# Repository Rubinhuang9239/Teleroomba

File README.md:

# Teleroomba

<h2>Info</h2>

A telepresence researching project that build for NYU NYC/Abu Dhabi/Shanghai campus.<br />
Thanks to Open Source Hardware Community, we hacked iRobot-Create roomba with Arduino(DFRobot Bluno), and created a telepresence robot.

<br/><br/>
This repo coontains the source code of the original project.
<br/>
For more documentation of this project, please visit: www.rubinhuang.com/#teleroomba

<h2>History + Future Development</h2>

<b>Teleroomba 1.x</b>

A 2D video and real time communication telepresence robot

<br />
The following image provides the concept of this project(teleroomba 1.x).<br/>

<br/>

It’s a roomba based robot which controlled from a web + Android + Arduino system.
User can control the robot from a web browser with keyboard input/mouse/touch screen.

<b>Teleroomba 2.x</b>

A 2D/3D video and real time communication telepresence robot

It’s a roomba based robot which controlled from a web + Android + Arduino system.
With the power of Lattepanda and Linux, this model is able to live stream a UV map from 360 camera like thetaS.

User can control the robot from a web browser with keyboard input/mouse/touch screen.
An individual window will stream the 360 video.

<b>Teleroomba 3.x</b>

A 2D/3D video and real time communication telepresence robot

A fully integrated system on Linux runs on lattepanda/raspberry Pi
support multi HDMI-Input/output, connect to live stream engine, webGL and even Unity game features.

<h2>Software and hardware structure</h2>
The following imgae shows current version of teleroomba(2.x)

<h2>Video and documentations</h2>

documented over iterations
<br/>
<b>Teleroomba 1.x</b>
<br/>
Video
<br/>

<br/>
Details
<br/>

<br/><br/>
<b>Teleroomba 2.x</b>
<br/>
Lattepanda + Node.js
<br/>

<h5>Circuit</h5>
<h5>Interface</h5>
More documentation in this link

<br /><br />
<h2>Hacking of the iRobot</h2>

<h3>Hacking documentation in google slides:</h3>

https://docs.google.com/presentation/d/1esRmssKKQKUmZPN4M6qO2HnMcj071nKUZhuvG29GHJI/edit?usp=sharing

<h3>Offical iRobot® Create® 2 Open Interface (OI):</h3>

http://www.irobotweb.com/~/media/MainSite/PDFs/About/STEM/Create/iRobot_Roomba_600_Open_Interface_Spec.pdf?la=en

<h2>Build</h2>
<a href = "https://github.com/Rubinhuang9239/Teleroomba/wiki/1.x-build-wiki">see 1.x build wiki</a>
<br/>
<a href = "https://github.com/Rubinhuang9239/Teleroomba/wiki/2.x-build-wiki">see 2.x build wiki</a>
<br/>

<h3>Control Manual</h3>
You can connect to turn server and call the mobile device on roomba(default auto connect and call) and establish bluetooth connection between the device & Roomba's serial port from control terminal. Full manual list here:
<br />
<ol>
<li>Connect with id</li>
<li>Call device with id</li>
<li>Bluno BLE scan</li>
<li>Restart safty mode</li>
<li>Serial board reset</li>
<li>Auto Docking</li>
</ol>

<h3>HUD display</h3>
<b>Distance</b>
A group of lines accroded to the perspective of the lense for helping driver to estimate the distance.

<b>Direction</b>
A rough predict of your crusing path, it will only show turning sign when roomba is doing same spot turning.

<h2>Credits + Resource</h2>

<h3>Credits + Thanks:</h3>
Early contributor:<br />
Rubin Huang<br />
Marc Abbey

Advising:<br />
Dan O'sullivan<br />
Shawn Van Every<br />

<h3>Current API:</h3>
coming soon....

<h3>More related projects:</h3>

<h5>From iRobot.com</h5>
http://www.irobot.com/About-iRobot/STEM/Create-2/Projects.aspx

<h5>From random hackers:</h5>

Johnny Chung Lee's DIY Telepresence Robot(2011)
with source code and intruductions
http://procrastineering.blogspot.com/2011/02/low-cost-video-chat-robot.html

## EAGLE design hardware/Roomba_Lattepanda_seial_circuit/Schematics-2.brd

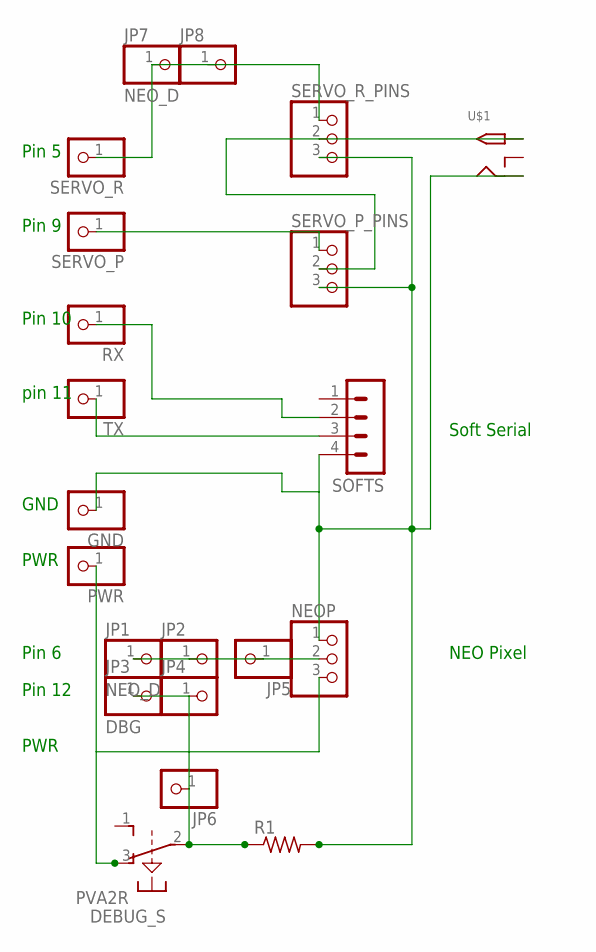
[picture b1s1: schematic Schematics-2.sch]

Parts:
DEBUG_S: PVA2R
GND: PINHD-1X1CB; 1X01-CLEANBIG
JP1, JP7: NEO_D; 1X01-CLEANBIG
JP2, JP4, JP5, JP6, JP8: PINHD-1X1CB; 1X01-CLEANBIG
JP3: DBG; 1X01-CLEANBIG
NEOP: PINHD-1X3CB; 1X03-CLEANBIG
PWR: PINHD-1X1CB; 1X01-CLEANBIG
R1: R-US_0204/7; 0204/7
RX: PINHD-1X1CB; 1X01-CLEANBIG
SERVO_P: PINHD-1X1CB; 1X01-CLEANBIG
SERVO_P_PINS: PINHD-1X3CB; 1X03-CLEANBIG
SERVO_R: PINHD-1X1CB; 1X01-CLEANBIG
SERVO_R_PINS: PINHD-1X3CB; 1X03-CLEANBIG
SOFTS: MA04-1
TX: PINHD-1X1CB; 1X01-CLEANBIG
U$1: 2.1MMJACKTHM; PJ-102A

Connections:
unnamed: RX.1, SOFTS.2
unnamed: JP1.1, JP2.1, JP5.1, NEOP.2
unnamed: SOFTS.3, TX.1
unnamed: GND.1, NEOP.1, R1.2, SERVO_P_PINS.3, SERVO_R_PINS.3, SOFTS.4, U$1.RING
unnamed: DEBUG_S.3 (O), NEOP.3, PWR.1
unnamed: DEBUG_S.2, JP3.1, JP4.1, JP6.1, R1.1
unnamed: SERVO_P_PINS.2, SERVO_R_PINS.2, U$1.TIP
unnamed: JP7.1, JP8.1, SERVO_R.1, SERVO_R_PINS.1
unnamed: SERVO_P.1, SERVO_P_PINS.1

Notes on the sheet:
Pin 10
pin 11
Pin 6
PWR
GND
Pin 12
Soft Serial
NEO Pixel
Pin 5
Pin 9

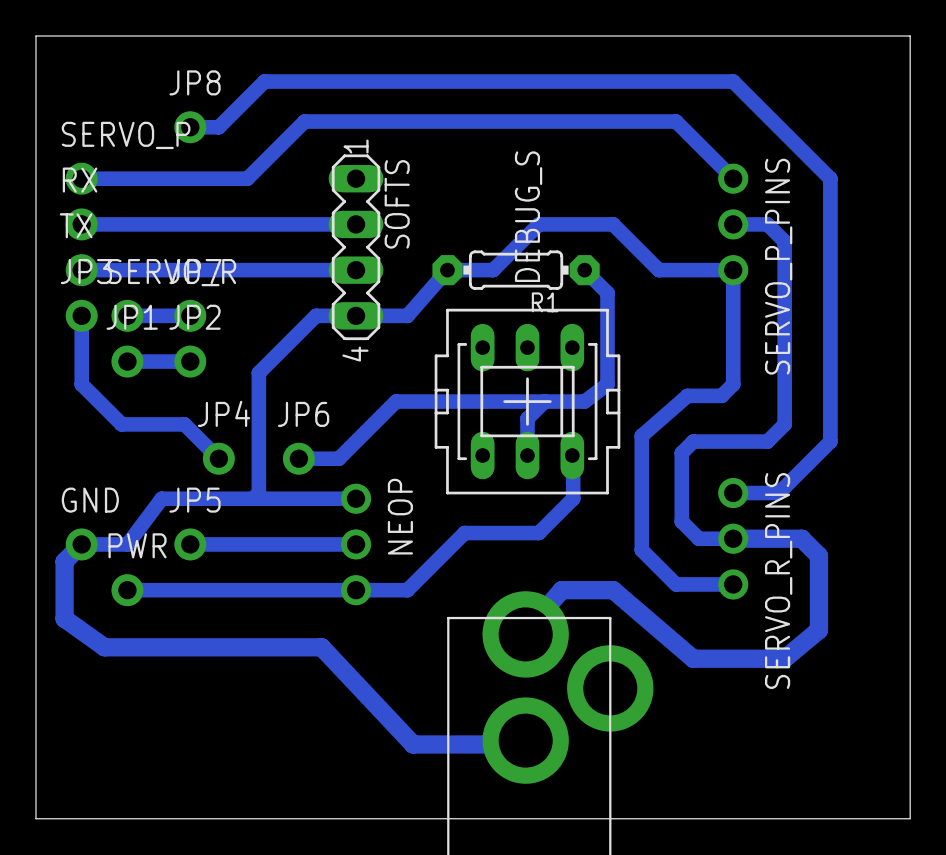
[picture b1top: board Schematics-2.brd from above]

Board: 2 copper layers, 48.6 x 43.5 mm, 21 parts (0 on the bottom side), 9 nets.

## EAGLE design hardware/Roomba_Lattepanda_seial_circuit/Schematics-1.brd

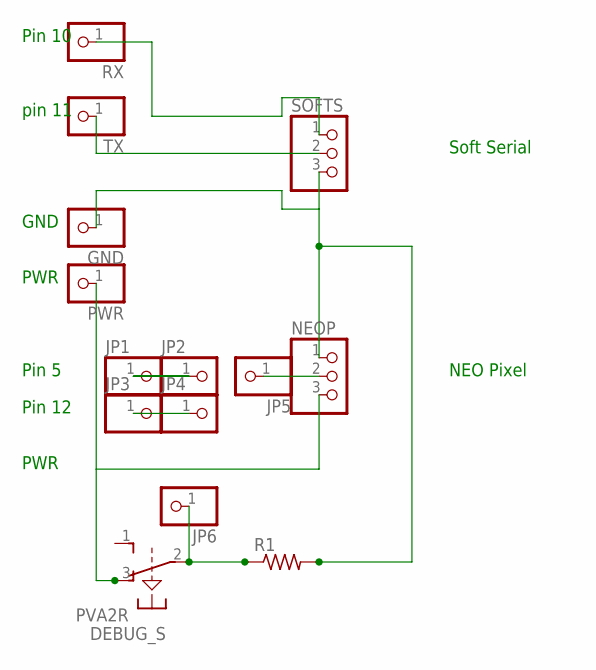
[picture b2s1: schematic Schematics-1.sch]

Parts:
DEBUG_S: PVA2R
GND: PINHD-1X1CB; 1X01-CLEANBIG
JP1, JP2, JP3, JP4, JP5, JP6: PINHD-1X1CB; 1X01-CLEANBIG
NEOP: PINHD-1X3CB; 1X03-CLEANBIG
PWR: PINHD-1X1CB; 1X01-CLEANBIG
R1: R-US_0204/7; 0204/7
RX: PINHD-1X1CB; 1X01-CLEANBIG
SOFTS: PINHD-1X3CB; 1X03-CLEANBIG
TX: PINHD-1X1CB; 1X01-CLEANBIG

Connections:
unnamed: RX.1, SOFTS.1
unnamed: JP1.1, JP2.1
unnamed: SOFTS.2, TX.1
unnamed: GND.1, NEOP.1, R1.2, SOFTS.3
unnamed: DEBUG_S.3 (O), NEOP.3, PWR.1
unnamed: DEBUG_S.2, JP6.1, R1.1
unnamed: JP5.1, NEOP.2
unnamed: JP3.1, JP4.1

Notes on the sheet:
Pin 10
pin 11
Pin 5
PWR
GND
Pin 12
Soft Serial
NEO Pixel

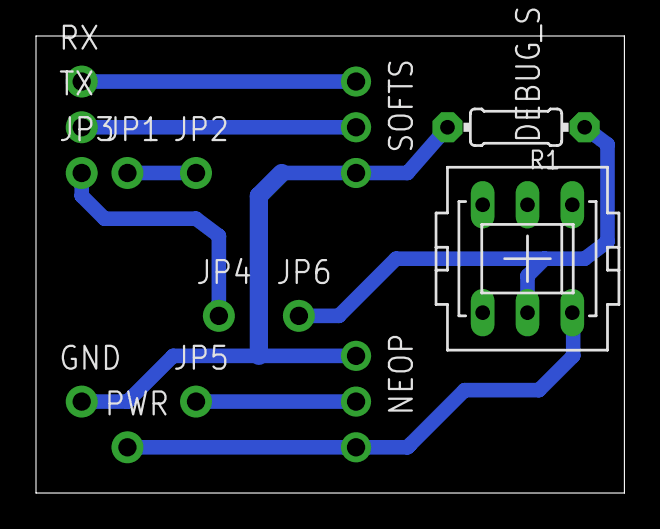
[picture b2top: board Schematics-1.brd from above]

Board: 2 copper layers, 32.7 x 25.4 mm, 14 parts (0 on the bottom side), 8 nets.

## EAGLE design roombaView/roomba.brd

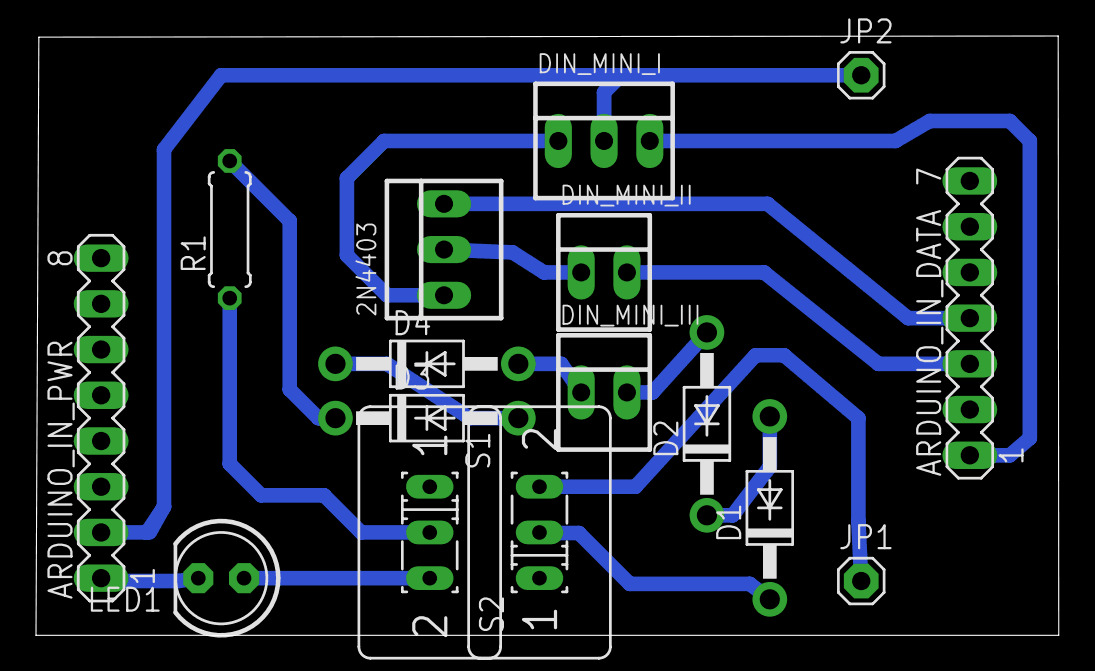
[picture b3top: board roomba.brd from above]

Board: 2 copper layers, 56.8 x 33.3 mm, 16 parts (0 on the bottom side), 16 nets.

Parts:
2N4403: 22-23-2031
ARDUINO_IN_DATA: MA07-1
ARDUINO_IN_PWR: MA08-1
D1, D2, D3, D4: 1N4001; DO41-10
DIN_MINI_I: 22-23-2031
DIN_MINI_II: 22-23-2021
DIN_MINI_III: 22-23-2021
JP1, JP2: 1X01
LED1: LED5MM
R1: 0207/7
S1, S2: M251

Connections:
unnamed: 2N4403.2, DIN_MINI_II.1
unnamed: 2N4403.1, DIN_MINI_I.1
unnamed: R1.1, S1.2
unnamed: D3.A, D4.C
unnamed: ARDUINO_IN_PWR.2, DIN_MINI_I.2, JP2.1
unnamed: 2N4403.3, ARDUINO_IN_DATA.4
unnamed: ARDUINO_IN_DATA.1, DIN_MINI_I.3
unnamed: ARDUINO_IN_DATA.3, DIN_MINI_II.2
unnamed: D4.A, DIN_MINI_III.1
unnamed: D2.A, DIN_MINI_III.2
unnamed: D1.A, D2.C
unnamed: LED1.A, S1.3
unnamed: ARDUINO_IN_PWR.1, LED1.K
unnamed: D1.C, S2.2
unnamed: D3.C, R1.2
unnamed: JP1.1, S2.3

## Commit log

2016-03-10 update app
2016-03-13 update source
2016-03-15 update with cordova
2016-03-27 update board
2016-04-07 adding slides
2016-04-07 update path structure
2016-04-07 adding oi
2016-04-07 add projects
2016-04-07 update readme....
2016-04-08 update WEBRTC source code
    yay
2016-04-08 update connection
    Auto BLE
2016-04-10 update documentation and folder structure
2016-04-16 add arts
2016-04-16 edit documentations
2016-04-16 update art
2016-04-18 upload arts
2016-04-25 push code
2016-05-09 https update
2016-06-01 update ble signs
2016-08-09 update local
    update local http/https;
    add 360 sphere view and webrtc connection
    add panda and webrtc connection
    add /role to express
    update panda, roomba, control, 360 with identity setup
    update roomba.js routing
2016-08-10 update video
2016-08-10 update file type
2016-08-10 add pandaServer prototype
2016-08-10 update 360 solution diagram
2016-08-10 panda_socket_to_serial
2016-10-01 update lattepanda arduino code
2016-10-02 update lattepanda arduino sys
2016-10-10 local server
2016-10-13 bug free serial
2016-10-14 update media player
2016-10-14 play remotely
2016-10-21 add new board/ add perfect stitch helper
2016-10-21 upload laser drawings
2016-10-23 add HUD
2016-10-23 add guide line and text
2016-10-24 update angle display / list display
2016-10-24 add reset Cam
2016-10-28 add resize function
2016-10-31 complete 360 stitchHelper
2016-11-01 full 360
2016-11-03 add ex 3d pro
2016-11-07 testing simpleSerial and servo control
2016-11-07 fuck git hub
2016-11-07 merge1
2016-11-08 upload working code
2016-11-10 logic tech update
2016-11-11 upload servo tower with https
2016-11-20 add new concept art to repo + fix the style of media list + toggle augment
2016-11-20 update read me
2016-11-20 ready update
2017-06-07 Update readme content
2017-06-07 Yeah
2017-06-07 Add new image
2017-07-19 update hardware
2017-08-01 Replace with server code and fix the rotation indicator
2017-08-22 Sync with the one on digital ocean
2017-08-29 Adding code for keyboard camera angel control
2017-08-29 Add view control code
2017-08-30 Update code for Login-EX3D to control the view of the Roomba
2017-08-31 Add sliders
2017-09-01 Finishing the update for 360 control
2017-09-06 Add led indicator direction
